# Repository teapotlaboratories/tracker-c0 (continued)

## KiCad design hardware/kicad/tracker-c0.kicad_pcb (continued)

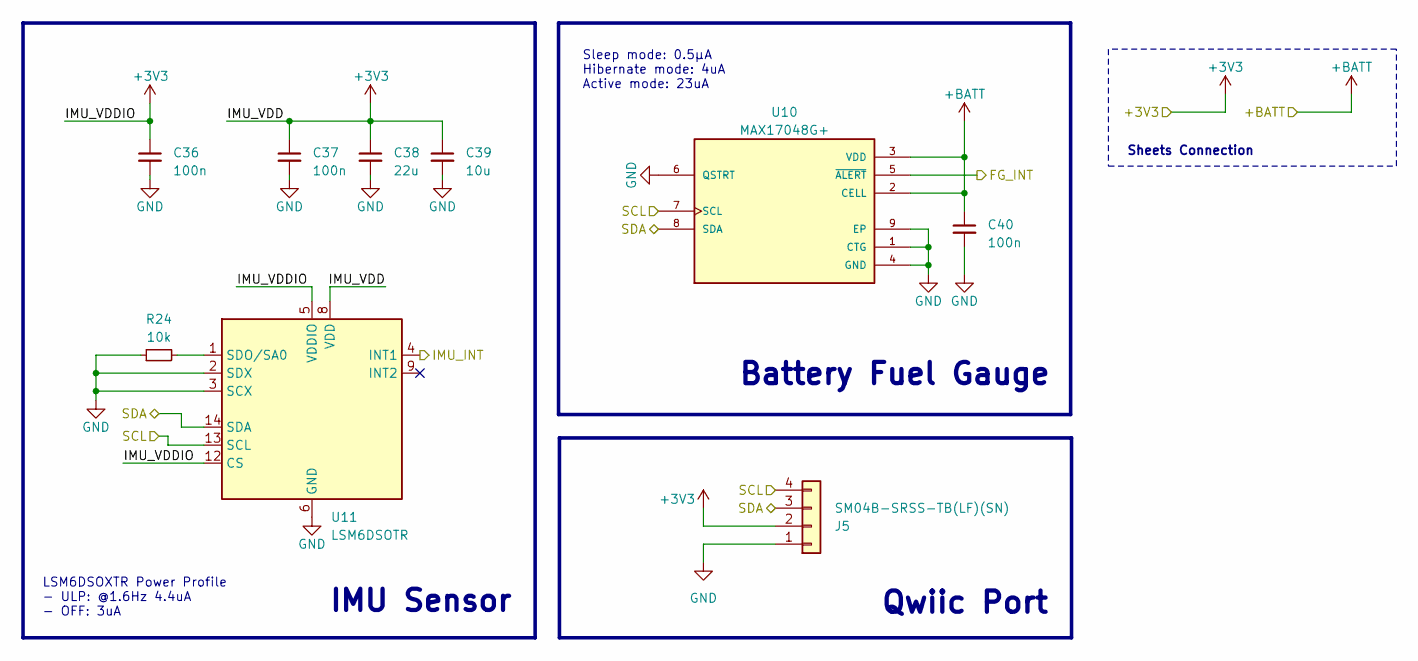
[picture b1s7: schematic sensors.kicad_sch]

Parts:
C36, C37, C40: 100n; C_0402_1005Metric; Manufacturer Part Number CL05B104KO5NNNC
C38: 22u; C_0603_1608Metric; Manufacturer Part Number CL10A226MQ8NRNC
C39: 10u; C_0603_1608Metric; Manufacturer Part Number CL10A106KP8NNNC
J5: SM04B-SRSS-TB(LF)(SN); JST_SH_SM04B-SRSS-TB_1x04-1MP_P1.00mm_Horizontal; Manufacturer Part Number SM04B-SRSS-TB(LF)(SN)
R24: 10k; R_0402_1005Metric; Manufacturer Part Number FRC0402F1002TS
U10: MAX17048G+; DFN-8-1EP_2x2mm_P0.5mm_EP0.7x1.3mm; Manufacturer Part Number MAX17048G+T10
U11: LSM6DSOTR; LGA-14_3x2.5mm_P0.5mm_LayoutBorder3x4y; Manufacturer Part Number LSM6DSOTR

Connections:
+3V3: C36.1, C37.1, C38.1, C39.1, J5.2, U11.5 (VDDIO), U11.8 (VDD), U11.12 (CS); also elsewhere on the board
+BATT: C40.1, U10.2 (CELL), U10.3 (VDD); also elsewhere on the board
/Main Controller/FG_INT: U10.5 (~ALERT); also elsewhere on the board
/Main Controller/IMU_INT: U11.4 (INT1); also elsewhere on the board
/Main Controller/SCL: J5.4, U10.7 (SCL), U11.13 (SCL); also elsewhere on the board
/Main Controller/SDA: J5.3, U10.8 (SDA), U11.14 (SDA); also elsewhere on the board
GND: C36.2, C37.2, C38.2, C39.2, C40.2, J5.1, R24.1, U10.1 (CTG), U10.4 (GND), U10.6 (QSTRT), U10.9 (EP), U11.2 (SDX), U11.3 (SCX), U11.6 (GND), U11.7 (GND); also elsewhere on the board
unnamed: R24.2, U11.1 (SDO/SA0)

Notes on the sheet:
IMU Sensor
LSM6DSOXTR Power Profile - ULP: @1.6Hz 4.4uA - OFF: 3uA
Battery Fuel Gauge
Qwiic Port
Sleep mode: 0.5µA Hibernate mode: 4uA Active mode: 23uA
Sheets Connection

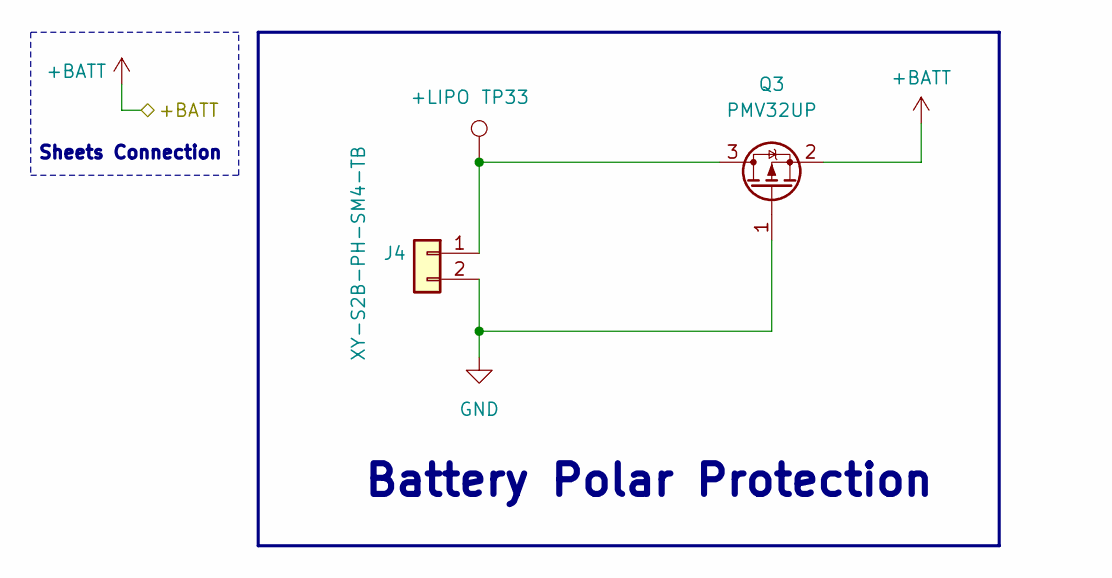
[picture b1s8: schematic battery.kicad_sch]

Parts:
J4: XY-S2B-PH-SM4-TB; JST_PH_S2B-PH-SM4-TB_1x02-1MP_P2.00mm_Horizontal; Manufacturer Part Number XY-S2B-PH-SM4-TB
Q3: PMV32UP; SOT-23; Part Description MOSFET P Channel 30V 4.3A 48mΩ@10V,4.3A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
TP33: +LIPO; TestPoint_Pad_D1.0mm

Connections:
+BATT: Q3.2 (S); also elsewhere on the board
GND: J4.2, Q3.1 (G); also elsewhere on the board
unnamed: J4.1, Q3.3 (D), TP33.1

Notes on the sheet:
Battery Polar Protection
Sheets Connection

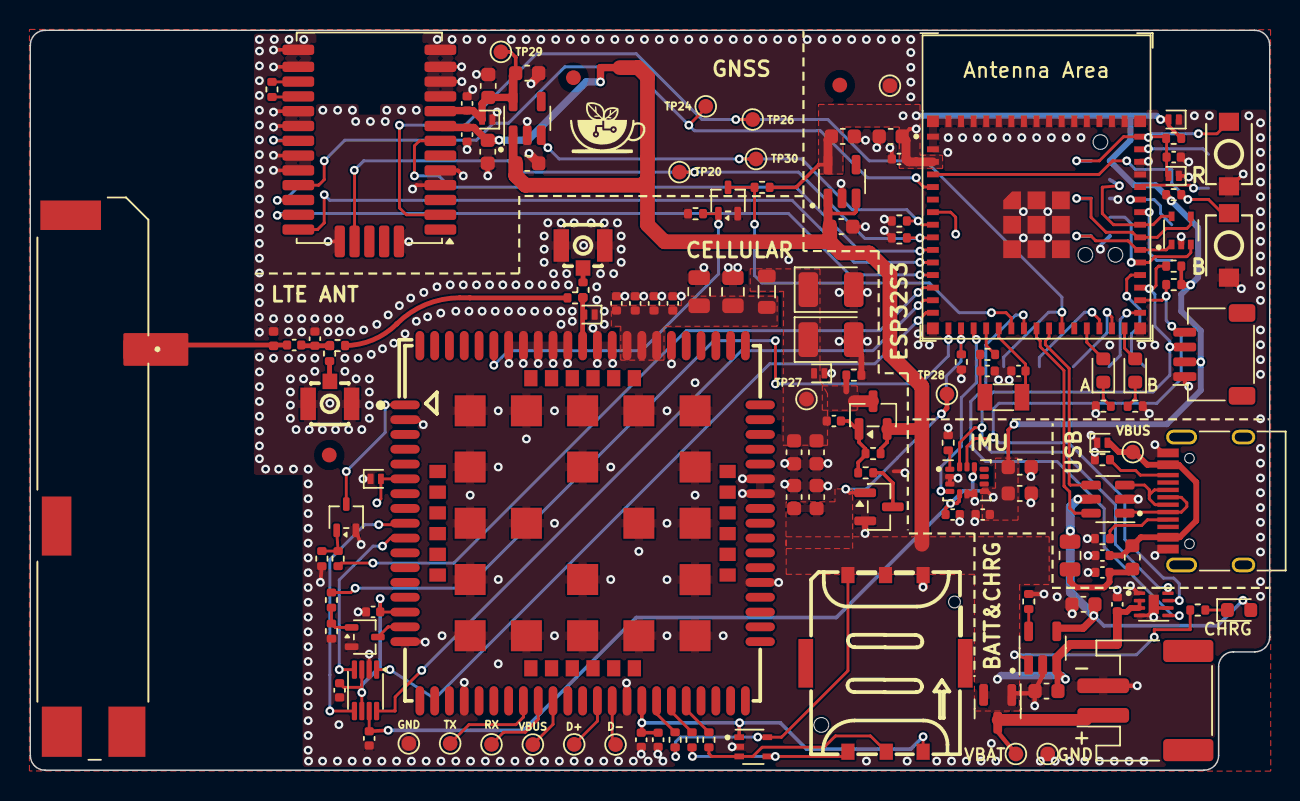
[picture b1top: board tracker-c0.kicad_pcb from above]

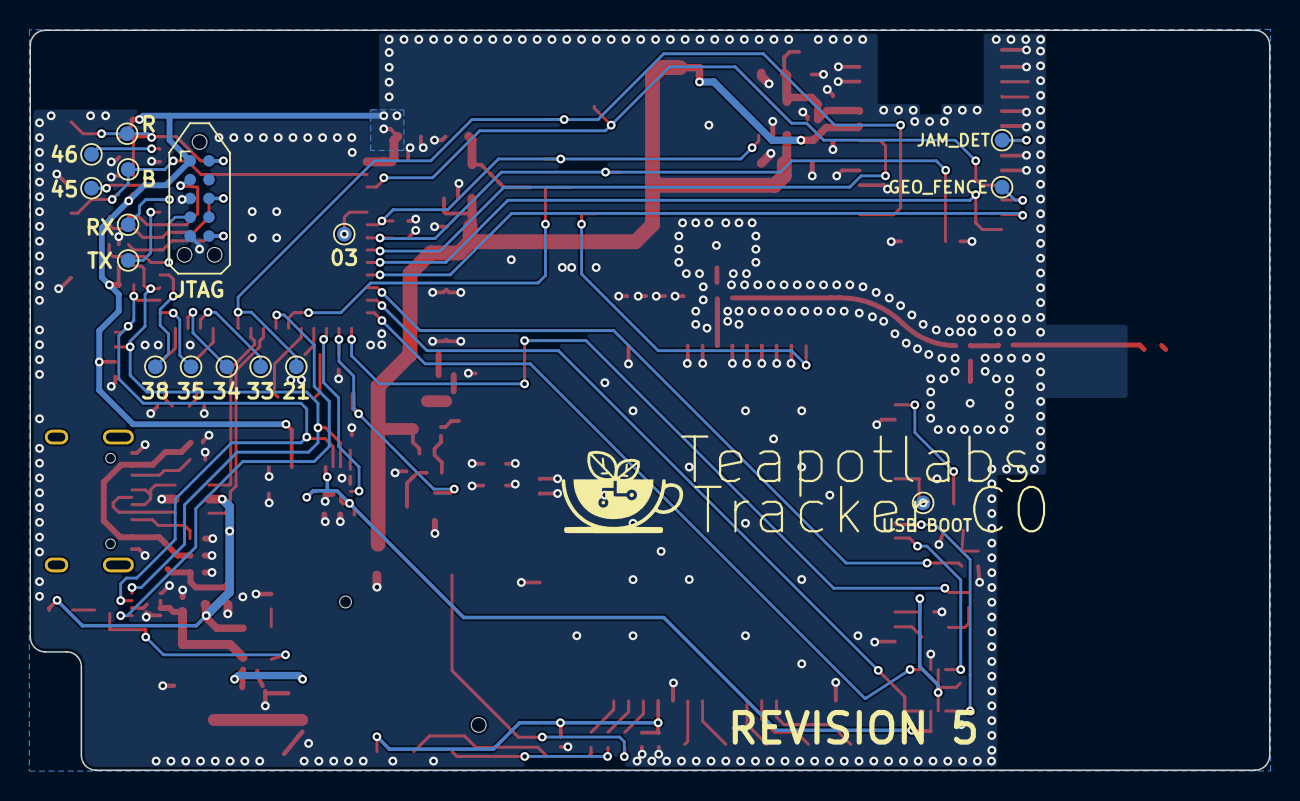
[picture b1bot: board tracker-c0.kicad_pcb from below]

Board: 4 copper layers, 83.8 x 50.0 mm, 152 parts (16 on the bottom side), 92 nets.

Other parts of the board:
FID1, FID2, FID3: Fiducial; Fiducial_1mm_Mask2mm

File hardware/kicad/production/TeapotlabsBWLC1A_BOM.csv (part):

Id,Reference,Qty,Manufacturer,Manufacturer Part Number,Value,Description,Datasheet,Footprint,Distributor,Distributor Part Number,Distributor Link
1,C1,1,Samsung Electro-Mechanics,CL05C100JB5NNNC,10p,10pF ±5% 50V Ceramic Capacitor C0G 0402,https://datasheet.lcsc.com/datasheet/pdf/02336ea48ea44ca18c7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,Capacitor_SMD:C_0402_1005Metric,LCSC,C32949,https://www.lcsc.com/product-detail/C32949.html
2,"C2,C9",2,FH (Guangdong Fenghua Advanced Tech),0402CG330J500NT,33p,50V 33pF C0G ±5% 0402 Multilayer Ceramic Capacitors MLCC - SMD/SMT ROHS,https://datasheet.lcsc.com/datasheet/pdf/09fe2daf22580a99fa7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,Capacitor_SMD:C_0402_1005Metric,LCSC,C1562,https://www.lcsc.com/product-detail/Multilayer-Ceramic-Capac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
3,"C3,C10,C11,C12,C13,C14,C16,C19,C33,C36,C37,C40",12,Samsung Electro-Mechanics,CL05B104KO5NNNC,100n,16V 100nF X7R ±10% 0402 Multilayer Ceramic Capacitors MLCC - SMD/SMT ROHS,https://datasheet.lcsc.com/datasheet/pdf/02336ea48ea44ca18c7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,Capacitor_SMD:C_0402_1005Metric,LCSC,C1525,https://www.lcsc.com/product-detail/Multilayer-Ceramic-Capac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
4,"C4,C21,C44",3,Samsung Electro-Mechanics,CL05A105KA5NQNC,1u,1uF ±10% 25V Ceramic Capacitor X5R 0402,https://datasheet.lcsc.com/datasheet/pdf/02336ea48ea44ca18c7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,Capacitor_SMD:C_0402_1005Metric,LCSC,C52923,https://www.lcsc.com/product-detail/C52923.html
5,"C5,C6",2,Murata Electronics,GRM21BR60J107ME15L,100u,6.3V 100uF X5R ±20% 0805 Multilayer Ceramic Capacitors MLCC - SMD/SMT ROHS,https://datasheet.lcsc.com/datasheet/pdf/b634458b2dd64f569dc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,Capacitor_SMD:C_0805_2012Metric,LCSC,C141660,https://www.lcsc.com/product-detail/Multilayer-Ceramic-Capac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
6,"C7,C8",2,KEMET,T520B337M006ATE040,330u,330uF 6.3V 40mΩ@100kHz ±20% CASE-B-3528 Tantalum Capacitors ROHS,https://datasheet.lcsc.com/datasheet/pdf/ea611ecc296046c4563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,Capacitor_Tantalum_SMD:CP_EIA-3528-21_Kemet-B,LCSC,C696806,https://www.lcsc.com/product-detail/Tantalum-Capacitors_KEME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
7,"C15,C18,C23,C26,C28,C29,C34,C35,C39",9,Samsung Electro-Mechanics,CL10A106KP8NNNC,10u,10V 10uF X5R ±10% 0603 Multilayer Ceramic Capacitors MLCC - SMD/SMT ROHS,https://datasheet.lcsc.com/datasheet/pdf/02336ea48ea44ca18c7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,Capacitor_SMD:C_0603_1608Metric,LCSC,C19702,https://www.lcsc.com/product-detail/Multilayer-Ceramic-Capac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
8,C17,1,Samsung Electro-Mechanics,CL10A475KO8NNNC,4u7,4.7uF ±10% 16V Ceramic Capacitor X5R 0603,https://datasheet.lcsc.com/datasheet/pdf/02336ea48ea44ca18c7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,Capacitor_SMD:C_0603_1608Metric,LCSC,C19666,https://www.lcsc.com/product-detail/C19666.html
9,"C20,C22",2,FH (Guangdong Fenghua Advanced Tech),0402CG220J500NT,22p,50V 22pF C0G ±5% 0402 Multilayer Ceramic Capacitors MLCC - SMD/SMT ROHS,https://datasheet.lcsc.com/datasheet/pdf/09fe2daf22580a99fa7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,Capacitor_SMD:C_0402_1005Metric,LCSC,C1555,https://www.lcsc.com/product-detail/C1555.html
10,"C24,C27",2,YAGEO,CC0603KRX7R9BB104,100n,100nF ±10% 50V Ceramic Capacitor X7R 0603,https://datasheet.lcsc.com/datasheet/pdf/23ccee80ee542e7cf15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,Capacitor_SMD:C_0603_1608Metric,LCSC,C14663,https://www.lcsc.com/product-detail/C14663.html
11,"C30,C31",2,Samsung Electro-Mechanics,CL10B105KA8NNNC,1u,1uF ±10% 25V Ceramic Capacitor X7R 0603,https://datasheet.lcsc.com/datasheet/pdf/02336ea48ea44ca18c7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,Capacitor_SMD:C_0603_1608Metric,LCSC,C29936,https://www.lcsc.com/product-detail/C29936.html
12,C32,1,Samsung Electro-Mechanics,CL05B103KB5NNNC,10n,10nF ±10% 50V Ceramic Capacitor X7R 0402,https://datasheet.lcsc.com/datasheet/pdf/02336ea48ea44ca18c7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,Capacitor_SMD:C_0402_1005Metric,LCSC,C15195,https://www.lcsc.com/product-detail/C15195.html
13,C38,1,Samsung Electro-Mechanics,CL10A226MQ8NRNC,22u,22uF ±20% 6.3V Ceramic Capacitor X5R 0603,https://datasheet.lcsc.com/datasheet/pdf/02336ea48ea44ca18c7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,Capacitor_SMD:C_0603_1608Metric,LCSC,C59461,https://www.lcsc.com/product-detail/C59461.html
14,C43,1,Murata Electronics,GRM1555C1H3R3CA01D,3p3,50V 3.3pF C0G 0402 Multilayer Ceramic Capacitors MLCC - SMD/SMT ROHS,https://datasheet.lcsc.com/datasheet/pdf/0fdfdb0f4d7947a757b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,Capacitor_SMD:C_0402_1005Metric,LCSC,C76968,https://www.lcsc.com/product-detail/Multilayer-Ceramic-Capac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
15,"D1,D3,D10",3,Leiditech,ESDBW5V0A1,ESDBW5V0A1,DFN1006 ESD Protection Devices ROHS,https://datasheet.lcsc.com/datasheet/pdf/37cc3b9a4497e223634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,Diode_SMD:D_SOD-882,LCSC,C5173252,https://www.lcsc.com/product-detail/span-style-background-co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
16,"D2,D7",2,TECH PUBLIC,ESDA6V1W5,ESDA6V1W5,10A 14V 150W 9V Unidirectional 5V SOT-353-5 ESD and Surge Protection (TVS/ESD) ROHS,https://datasheet.lcsc.com/datasheet/pdf/5450ddd25002671c4f0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,Package_TO_SOT_SMD:SOT-353_SC-70-5,LCSC,C3040609,https://www.lcsc.com/product-detail/span-style-background-co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
17,"D4,D8,D9",3,TECH PUBLIC,ESD5651N,ESD5651N,DFN1006-2L ESD and Surge Protection (TVS/ESD) ROHS,https://datasheet.lcsc.com/datasheet/pdf/2c19d3aab1c204b8ee5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,Diode_SMD:D_SOD-882,LCSC,C5342369,https://www.lcsc.com/product-detail/span-style-background-co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
18,D5,1,Lite-On,LTST-C191KGKT,LTST-C191KGKT,20mA 35mcd -55℃~+85℃ 567.5nm~576.5nm Green-yellow 130° 75mW 2V 0603 Light Emitting Diodes (LED) ROHS,https://datasheet.lcsc.com/datasheet/pdf/1767ff17728a42c5853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,LED_SMD:LED_0603_1608Metric,LCSC,C125098,https://www.lcsc.com/product-detail/Light-Emitting-Diodes-LE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
19,D6,1,Lite-On,LTST-C191KRKT,LTST-C191KRKT,20mA 54mcd -55℃~+85℃ 631nm Red 130° 75mW 2V 0603 Light Emitting Diodes (LED) ROHS,https://datasheet.lcsc.com/datasheet/pdf/d51ae7f7d38f4d17a71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,LED_SMD:LED_0603_1608Metric,LCSC,C125099,https://www.lcsc.com/product-detail/Light-Emitting-Diodes-LE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
20,D11,1,EKINGLUX,E6C0603SEAC1UDA,E6C0603SEAC1UDA,Colorless transparence -40℃~+90℃ 605nm Orange 120° 0603 Light Emitting Diodes (LED),https://datasheet.lcsc.com/datasheet/pdf/4b7455c7c4ef852ab45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,LED_SMD:LED_0603_1608Metric,LCSC,C375450,https://www.lcsc.com/product-detail/Light-Emitting-Diodes-LE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
21,E1,1,TE Connectivity,2108784-1,2108784-1,"Antennas PCB ANTENNA, SMD 698-6000MHz",https://www.te.com/commerce/DocumentDelivery/DDEController?A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,bwlc1a:2108784-1,Mouser,571-2108784-1,https://www.mouser.com/ProductDetail/TE-Connectivity/2108784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
22,F1,1,RUILON(Shenzhen Ruilongyuan Elec),SMD0805P075TF,SMD0805P075TF,6V 750mA 40A 1.5A 0805 Resettable Fuses ROHS,https://datasheet.lcsc.com/datasheet/pdf/951ee7e7633b21be8a3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,Fuse:Fuse_0805_2012Metric,LCSC,C20979,https://www.lcsc.com/product-detail/Resettable-Fuses_RUILON-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
23,FB1,1,Murata Electronics,BLM21PG300SN1D,BLM21PG300SN1D,14mΩ ±25% 30Ω@100MHz 0805 Ferrite Beads ROHS,https://datasheet.lcsc.com/datasheet/pdf/1addff62e5484bf39ea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,Inductor_SMD:L_0805_2012Metric,LCSC,C16903,https://www.lcsc.com/product-detail/Ferrite-Beads_Murata-Ele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
24,FB2,1,Murata Electronics,BLM18PG121SN1D,BLM18PG121SN1D,120Ω@100MHz 1 Line Ferrite Bead 0603 2A 50mΩ,https://datasheet.lcsc.com/datasheet/pdf/fa365b03943947af82e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,Inductor_SMD:L_0603_1608Metric,LCSC,C14709,https://www.lcsc.com/product-detail/C14709.html
25,J1,1,XUNPU,SMN-304,SMN-304,Pluggable Gold 1.35mm Deck -40℃~+85℃ 260℃ NanoSIM SMD SIM Card Connectors ROHS,https://datasheet.lcsc.com/datasheet/pdf/5e1d08f1fc7d3f86c4b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,bwlc1a:SIM-SMD_SMN-304,LCSC,C266889,https://www.lcsc.com/product-detail/SIM-Card-Connectors_XUNP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
26,J3,1,Korean Hroparts Elec,TYPE-C-31-M-12,USB_C_Receptacle_USB2.0,5A 1 16P Female Type-C SMD USB Connectors ROHS,https://datasheet.lcsc.com/datasheet/pdf/9e56b777c022540fcce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,Connector_USB:USB_C_Receptacle_HRO_TYPE-C-31-M-12,LCSC,C165948,https://www.lcsc.com/product-detail/span-style-background-co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
27,J4,1,XYECONN,XY-S2B-PH-SM4-TB,XY-S2B-PH-SM4-TB,"1x2P PH 2.0mm Surface Mount Right Angle Wafer, 2A 250V, -25℃~+85℃ (JST S2B-PH-SM4-TB compatible)",https://datasheet.lcsc.com/datasheet/pdf/989811e30ec9c4bae1f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,bwlc1a:JST_PH_S2B-PH-SM4-TB_1x02-1MP_P2.00mm_Horizontal,LCSC,C54582899,https://www.lcsc.com/product-detail/C54582899.html
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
